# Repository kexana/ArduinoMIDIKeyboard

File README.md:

# ArduinoMIDIKeyboard
Refurbishing old toy keyboard to be MIDI compatible using arduino (serial write)

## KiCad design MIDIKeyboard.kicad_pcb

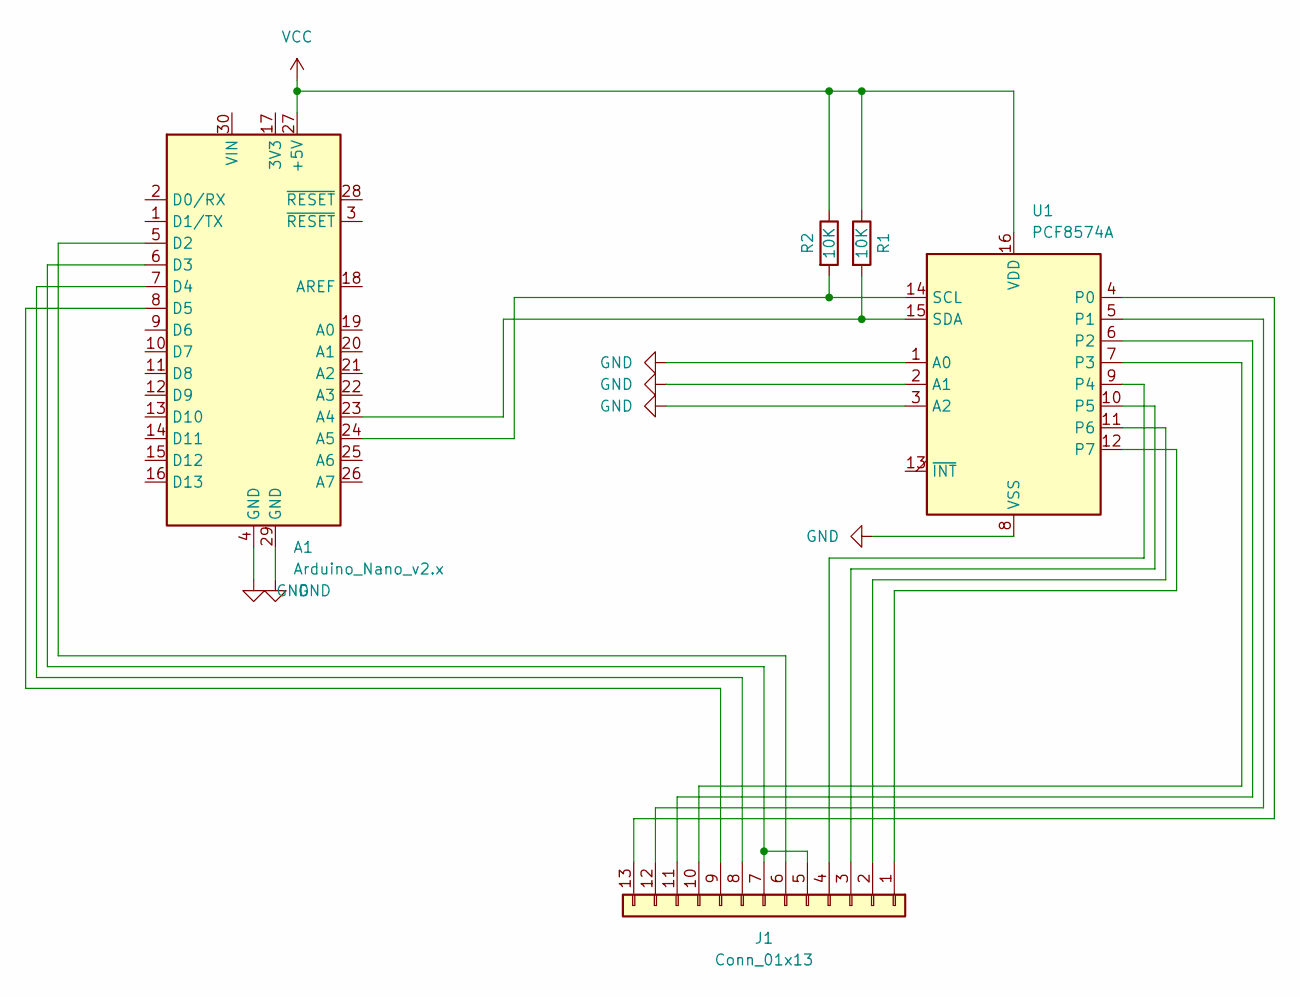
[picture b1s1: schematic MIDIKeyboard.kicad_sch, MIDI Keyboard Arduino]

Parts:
A1: Arduino_Nano_v2.x; Arduino_Nano_WithMountingHoles
J1: Conn_01x13; PinSocket_1x13_P2.54mm_Vertical
R1, R2: 10K; R_Axial_DIN0207_L6.3mm_D2.5mm_P10.16mm_Horizontal
U1: PCF8574A; DIP-16_W7.62mm_Socket

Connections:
GND: A1.4 (GND), A1.29 (GND), U1.1 (A0), U1.2 (A1), U1.3 (A2), U1.8 (VSS)
unnamed: A1.5 (D2), J1.6
unnamed: A1.6 (D3), J1.5, J1.7
unnamed: A1.7 (D4), J1.8
unnamed: A1.8 (D5), J1.9
unnamed: A1.23 (A4), R1.2, U1.15 (SDA)
unnamed: A1.24 (A5), R2.2, U1.14 (SCL)
unnamed: J1.1, U1.12 (P7)
unnamed: J1.2, U1.11 (P6)
unnamed: J1.3, U1.10 (P5)
unnamed: J1.4, U1.9 (P4)
unnamed: J1.10, U1.7 (P3)
unnamed: J1.11, U1.6 (P2)
unnamed: J1.12, U1.5 (P1)
unnamed: J1.13, U1.4 (P0)
VCC: A1.27 (+5V), R1.1, R2.1, U1.16 (VDD)

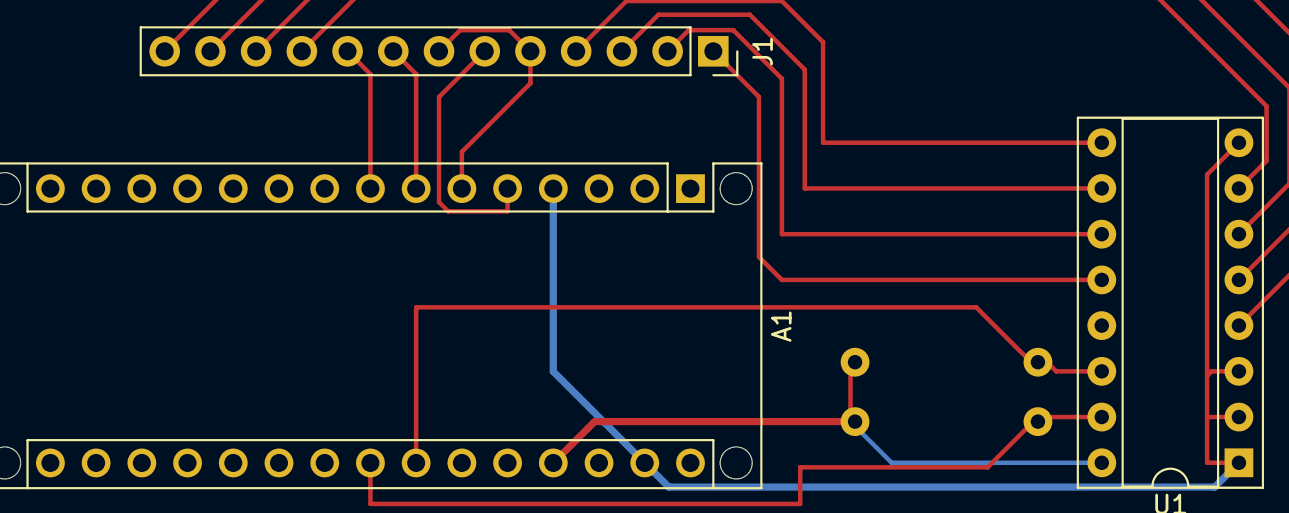
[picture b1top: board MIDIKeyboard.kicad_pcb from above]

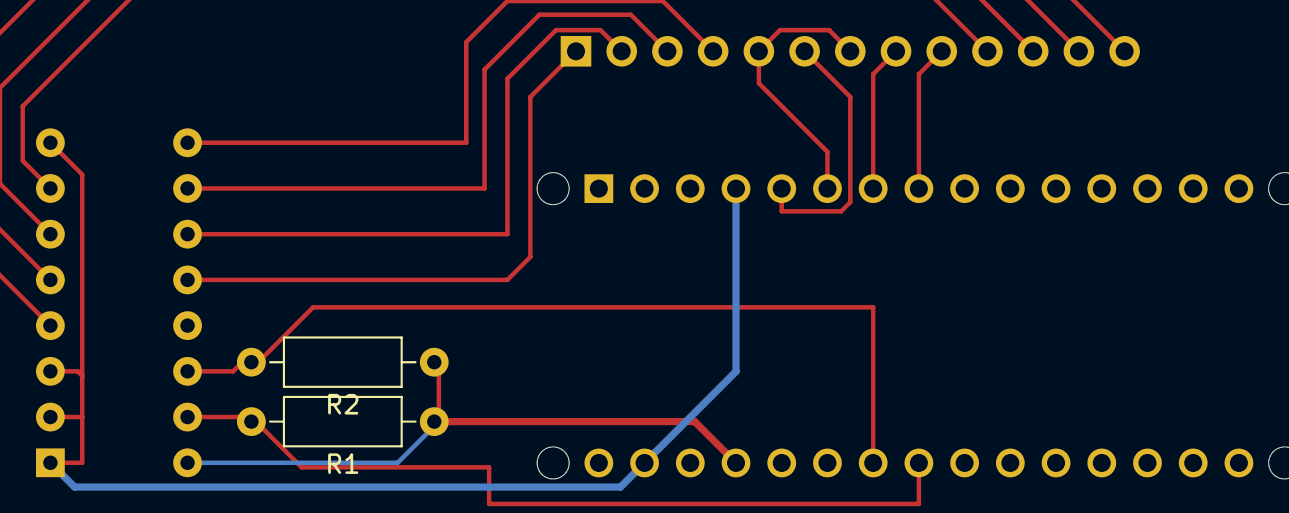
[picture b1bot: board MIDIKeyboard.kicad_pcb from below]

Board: 2 copper layers, 5 parts (2 on the bottom side), 16 nets.

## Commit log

2022-06-25 code commit
2022-06-25 adding PCB layout and schematic
